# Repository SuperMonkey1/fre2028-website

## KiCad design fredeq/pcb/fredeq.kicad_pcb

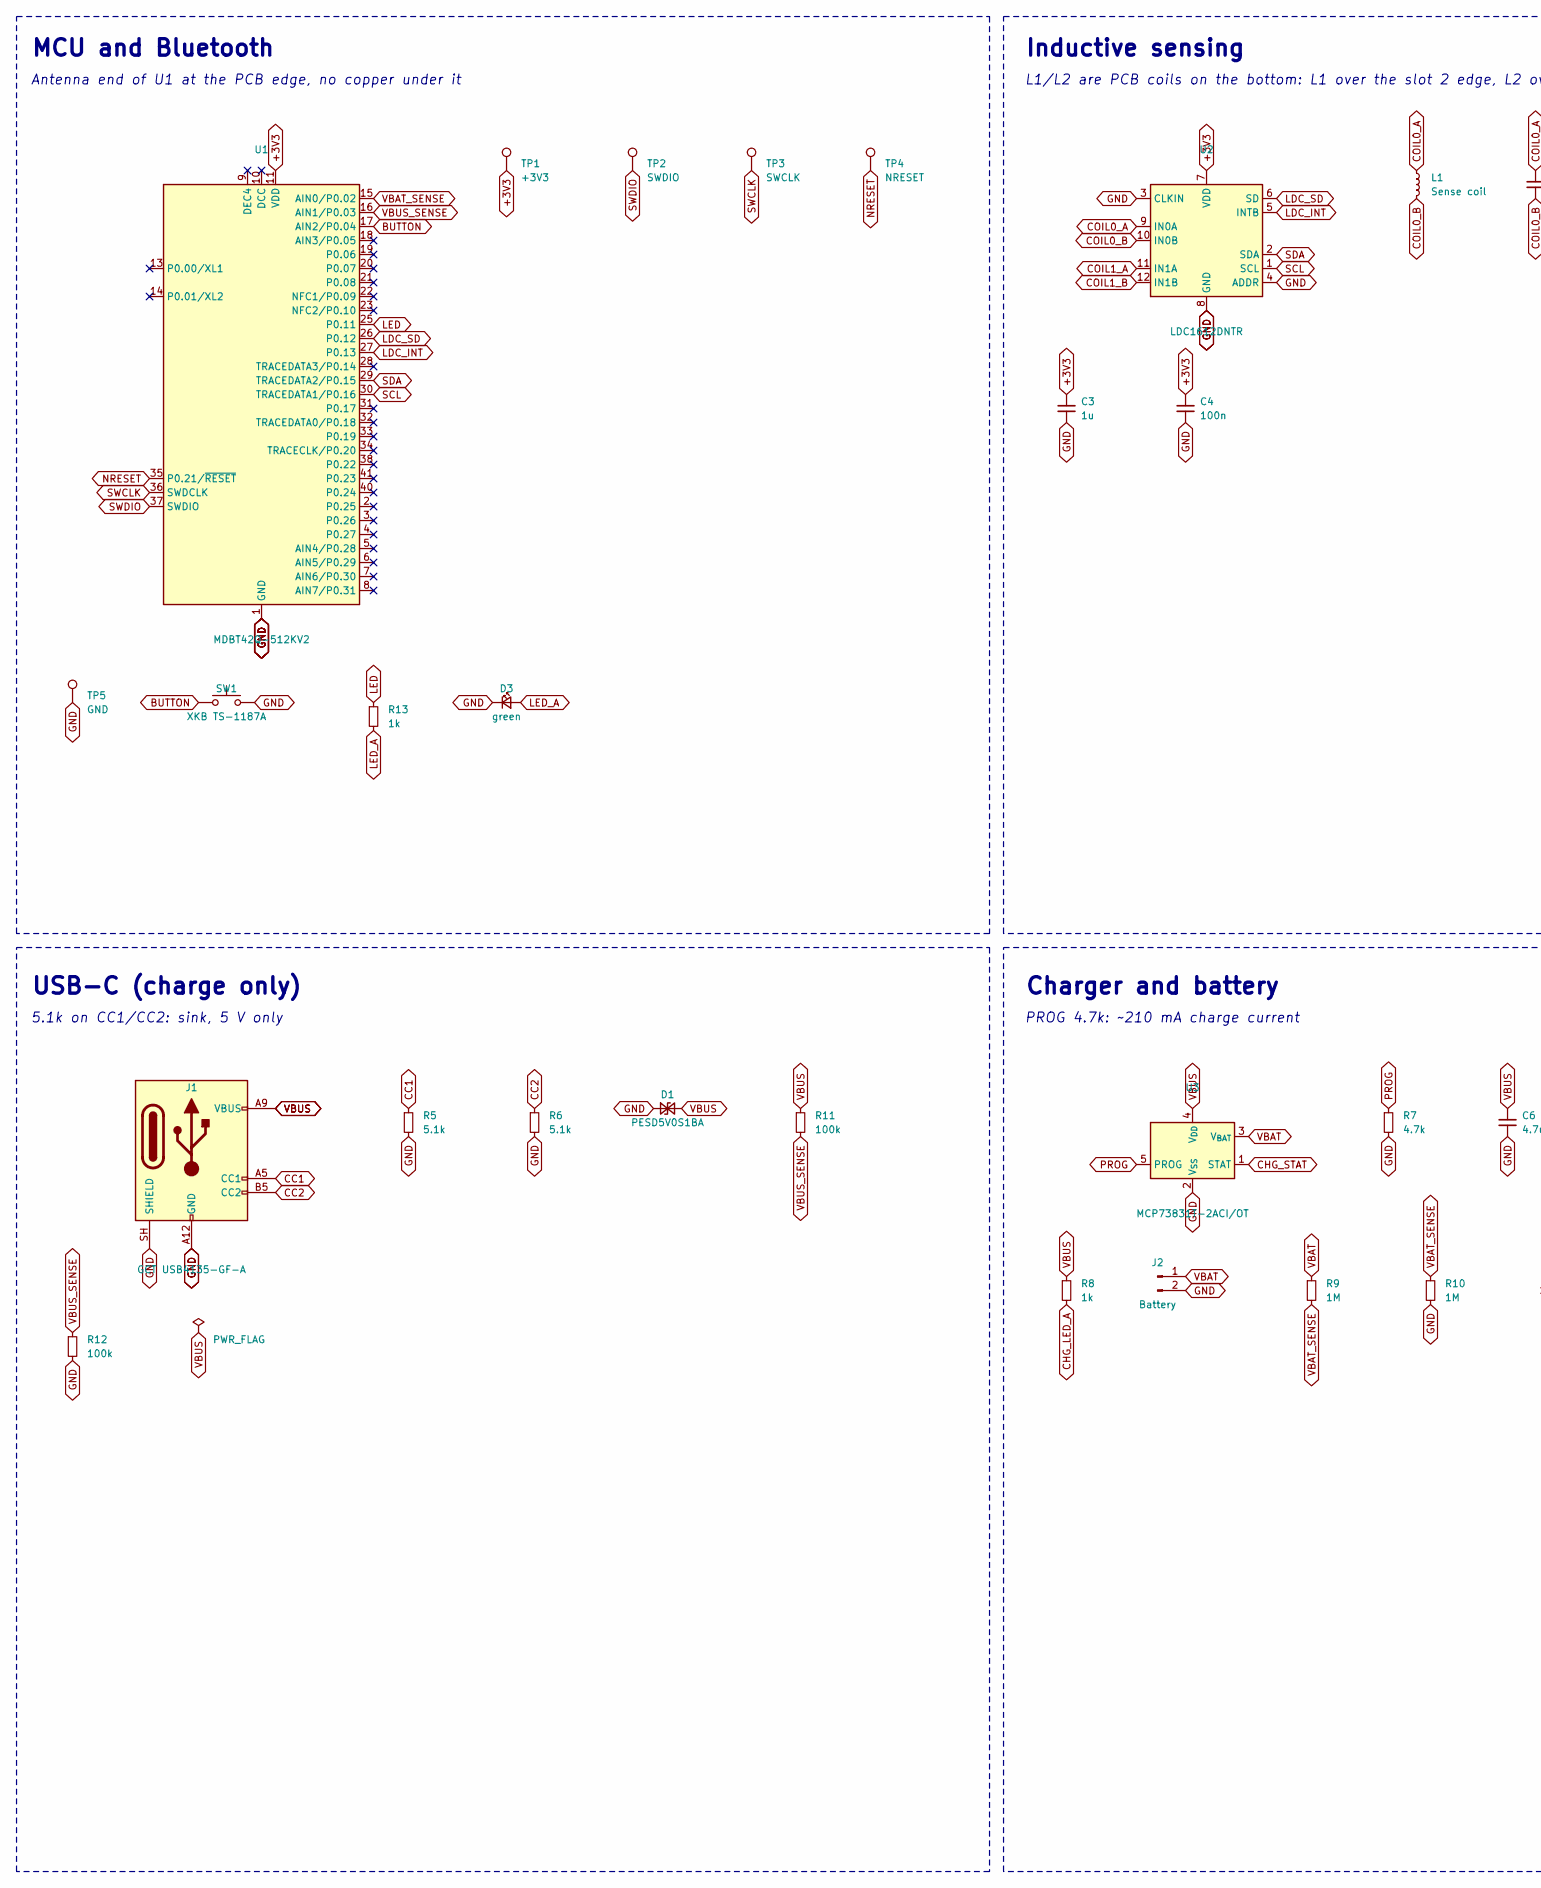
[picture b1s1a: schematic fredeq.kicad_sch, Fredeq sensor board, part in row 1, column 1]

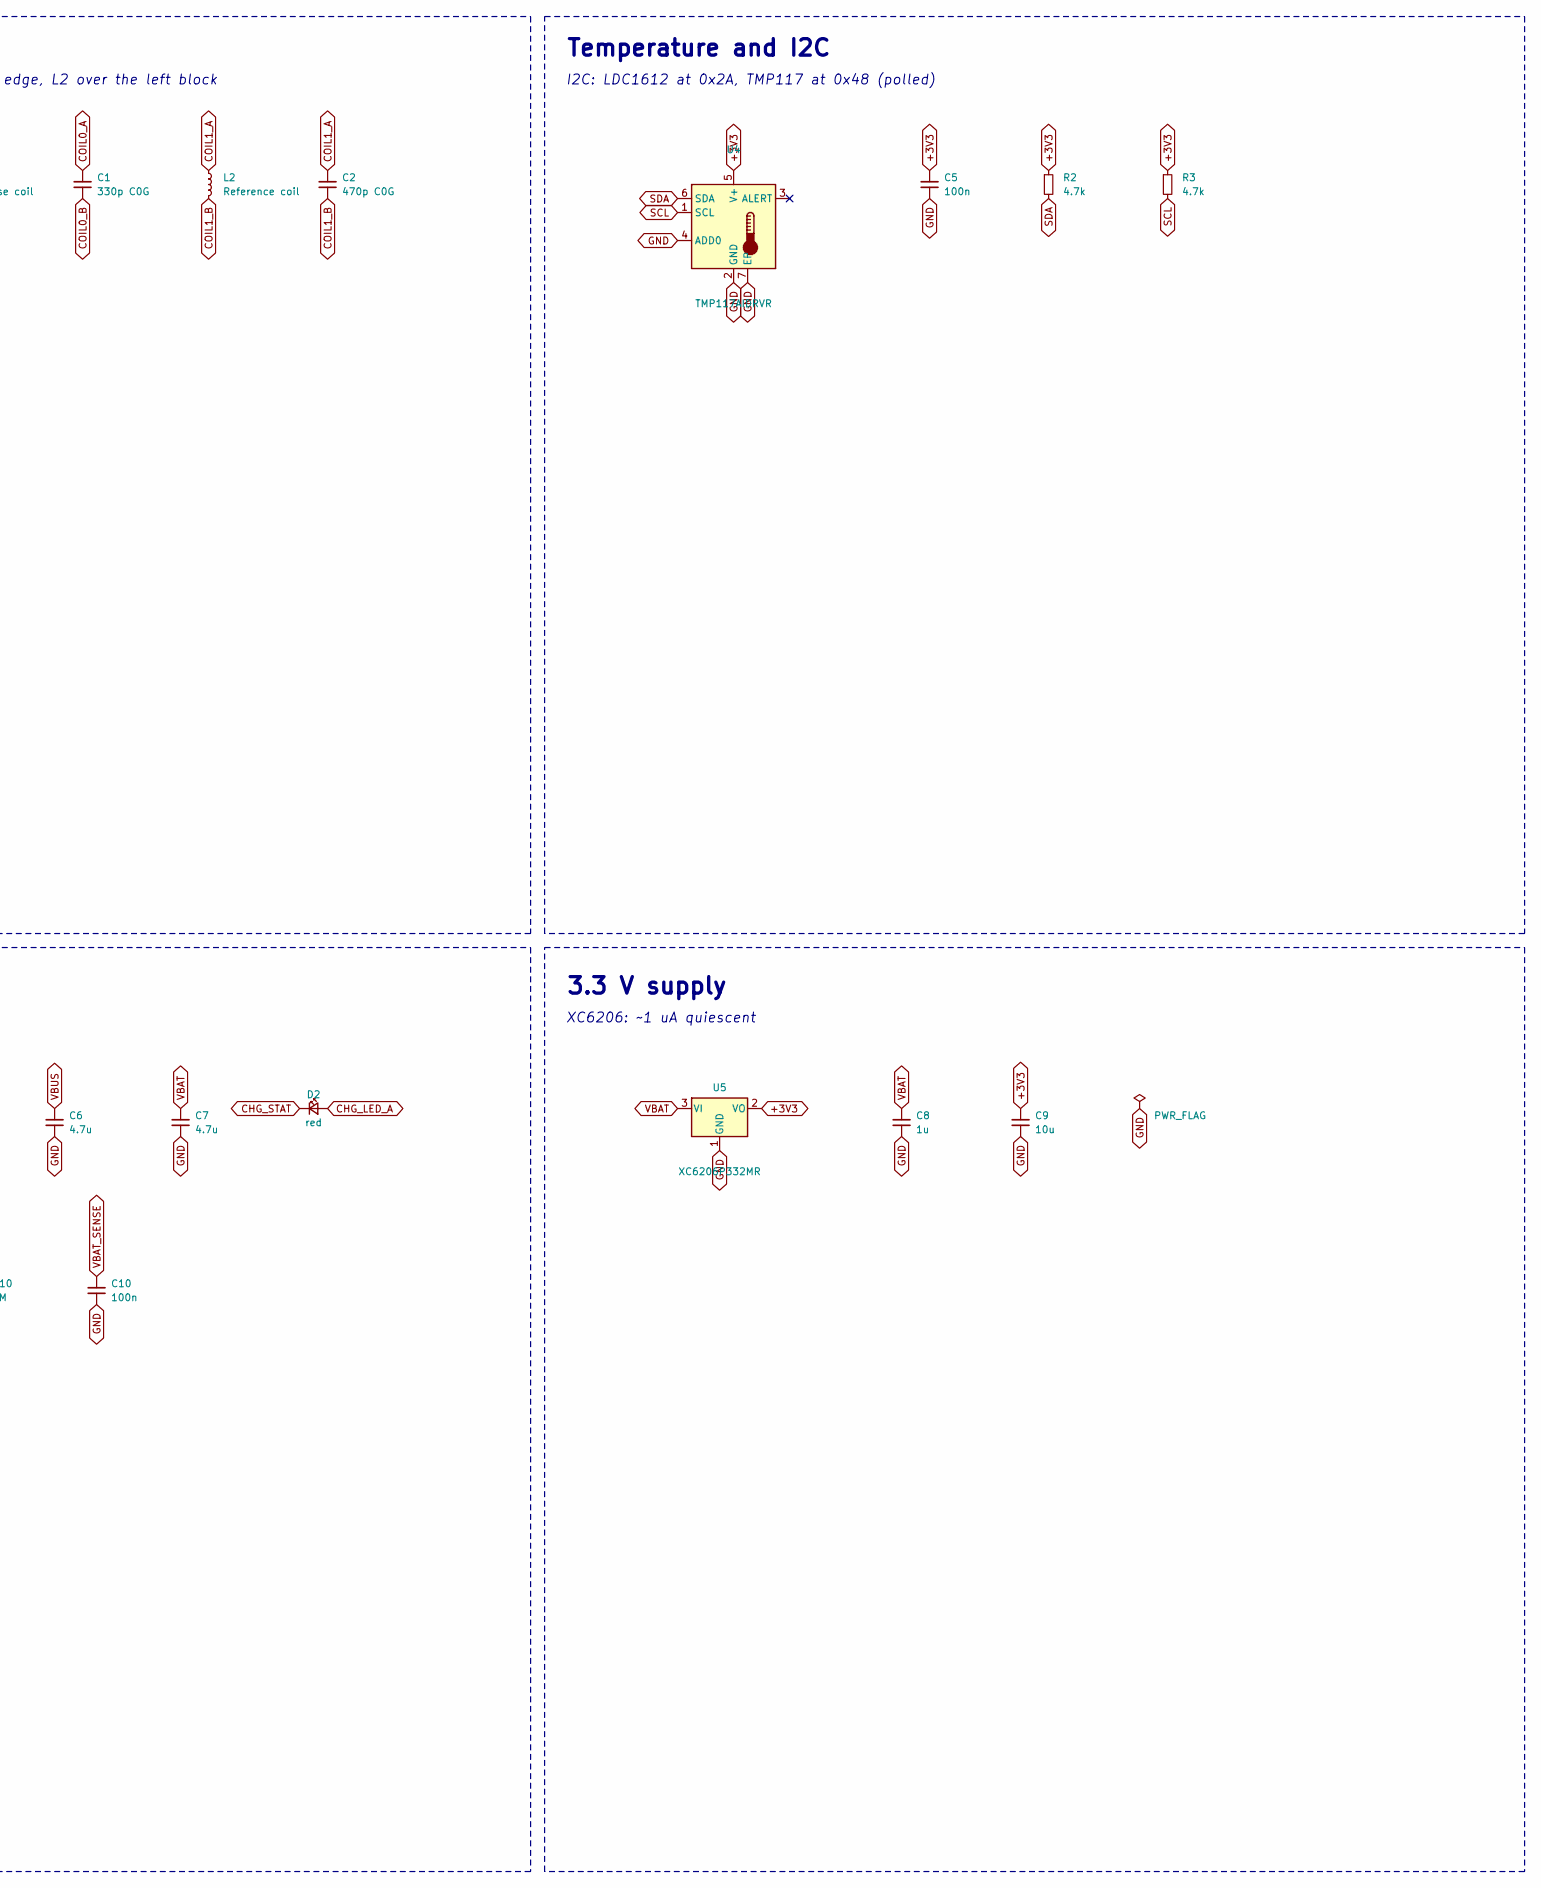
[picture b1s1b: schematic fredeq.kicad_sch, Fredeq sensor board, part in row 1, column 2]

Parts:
C1: 330p C0G; C_0402_1005Metric
C2: 470p C0G; C_0402_1005Metric
C3, C8: 1u; C_0402_1005Metric
C4, C5, C10: 100n; C_0402_1005Metric
C6, C7: 4.7u; C_0603_1608Metric
C9: 10u; C_0603_1608Metric
D1: PESD5V0S1BA; D_SOD-323
D2: red; LED_0603_1608Metric
D3: green; LED_0603_1608Metric
J1: GCT USB4135-GF-A; USB_C_Receptacle_GCT_USB4135-GF-A_6P_TopMnt_Horizontal
J2: Battery; JST_SH_SM02B-SRSS-TB_1x02-1MP_P1.00mm_Horizontal
L1: Sense coil; Coil_Sense_6x9mm
L2: Reference coil; Coil_Ref_4.4x10mm
R2, R3, R7: 4.7k; R_0402_1005Metric
R5, R6: 5.1k; R_0402_1005Metric
R8, R13: 1k; R_0402_1005Metric
R9, R10: 1M; R_0402_1005Metric
R11, R12: 100k; R_0402_1005Metric
SW1: XKB TS-1187A; SW_Push_1P1T_XKB_TS-1187A
TP1: +3V3; TestPoint_Pad_D1.0mm
TP2: SWDIO; TestPoint_Pad_D1.0mm
TP3: SWCLK; TestPoint_Pad_D1.0mm
TP4: NRESET; TestPoint_Pad_D1.0mm
TP5: GND; TestPoint_Pad_D1.0mm
U1: MDBT42Q-512KV2; Raytac_MDBT42Q
U2: LDC1612DNTR; WSON-12-1EP_4x4mm_P0.5mm_EP2.6x3mm
U3: MCP73831T-2ACI/OT; SOT-23-5
U4: TMP117AIDRVR; WSON-6-1EP_2x2mm_P0.65mm_EP1x1.6mm
U5: XC6206P332MR; SOT-23-3

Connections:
+3V3: C3.1, C4.1, C5.1, C9.1, R2.1, R3.1, TP1.1, U1.11 (VDD), U2.7 (VDD), U4.5 (V+), U5.2 (VO)
BUTTON: SW1.1, U1.17 (AIN2/P0.04)
CC1: J1.A5 (CC1), R5.1
CC2: J1.B5 (CC2), R6.1
CHG_LED_A: D2.2 (A), R8.2
CHG_STAT: D2.1 (K), U3.1 (STAT)
COIL0_A: C1.1, L1.1, U2.9 (IN0A)
COIL0_B: C1.2, L1.2, U2.10 (IN0B)
COIL1_A: C2.1, L2.1, U2.11 (IN1A)
COIL1_B: C2.2, L2.2, U2.12 (IN1B)
GND: C3.2, C4.2, C5.2, C6.2, C7.2, C8.2, C9.2, C10.2, D1.1 (A1), D3.1 (K), J1.A12 (GND), J1.B12 (GND), J1.SH (SHIELD), J2.2, R5.2, R6.2, R7.2, R10.2, R12.2, SW1.2, TP5.1, U1.1 (GND), U1.12 (GND), U1.24 (GND), U1.39 (GND), U2.3 (CLKIN), U2.4 (ADDR), U2.8 (GND), U2.13 (GND), U3.2 (V_{SS}), U4.2 (GND), U4.4 (ADD0), U4.7 (EP), U5.1 (GND)
LDC_INT: U1.27 (P0.13), U2.5 (INTB)
LDC_SD: U1.26 (P0.12), U2.6 (SD)
LED: R13.1, U1.25 (P0.11)
LED_A: D3.2 (A), R13.2
NRESET: TP4.1, U1.35 (P0.21/~RESET)
PROG: R7.1, U3.5 (PROG)
SCL: R3.2, U1.30 (TRACEDATA1/P0.16), U2.1 (SCL), U4.1 (SCL)
SDA: R2.2, U1.29 (TRACEDATA2/P0.15), U2.2 (SDA), U4.6 (SDA)
SWCLK: TP3.1, U1.36 (SWDCLK)
SWDIO: TP2.1, U1.37 (SWDIO)
VBAT: C7.1, C8.1, J2.1, R9.1, U3.3 (V_{BAT}), U5.3 (VI)
VBAT_SENSE: C10.1, R9.2, R10.1, U1.15 (AIN0/P0.02)
VBUS: C6.1, D1.2 (A2), J1.A9 (VBUS), J1.B9 (VBUS), R8.1, R11.1, U3.4 (V_{DD})
VBUS_SENSE: R11.2, R12.1, U1.16 (AIN1/P0.03)

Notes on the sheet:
MCU and Bluetooth
Antenna end of U1 at the PCB edge, no copper under it
Inductive sensing
L1/L2 are PCB coils on the bottom: L1 over the slot 2 edge, L2 over the left block
Temperature and I2C
I2C: LDC1612 at 0x2A, TMP117 at 0x48 (polled)
USB-C (charge only)
5.1k on CC1/CC2: sink, 5 V only
Charger and battery
PROG 4.7k: ~210 mA charge current
3.3 V supply
XC6206: ~1 uA quiescent

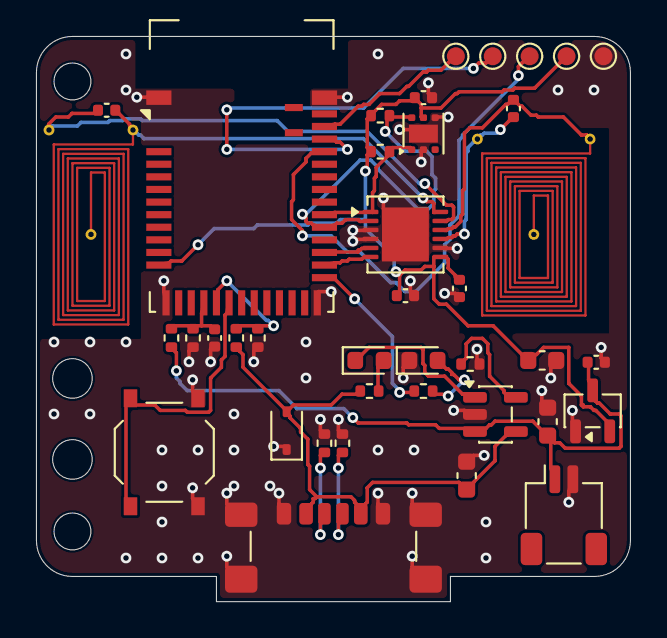
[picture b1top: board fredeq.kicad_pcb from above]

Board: 2 copper layers, 33.0 x 31.4 mm, 43 parts (0 on the bottom side), 25 nets.

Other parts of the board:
H1, H4: Hole_Pin_2.05mm
H2, H3: Hole_M2_Screw

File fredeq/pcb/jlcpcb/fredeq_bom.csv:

Comment,Designator,Footprint,LCSC Part #
330p C0G,C1,C_0402_1005Metric,C5591231
470p C0G,C2,C_0402_1005Metric,C75274
1u,"C3,C8",C_0402_1005Metric,C52923
100n,"C4,C5,C10",C_0402_1005Metric,C1525
4.7u,"C6,C7",C_0603_1608Metric,C19666
10u,C9,C_0603_1608Metric,C19702
PESD5V0S1BA,D1,D_SOD-323,C19224
red,D2,LED_0603_1608Metric,C2286
green,D3,LED_0603_1608Metric,C72043
Battery,J2,JST_SH_SM02B-SRSS-TB_1x02-1MP_P1.00mm_Horizontal,C160402
100k,"R11,R12",R_0402_1005Metric,C25741
4.7k,"R2,R3,R7",R_0402_1005Metric,C25900
5.1k,"R5,R6",R_0402_1005Metric,C25905
1k,"R8,R13",R_0402_1005Metric,C11702
1M,"R9,R10",R_0402_1005Metric,C26083
XKB TS-1187A,SW1,SW_Push_1P1T_XKB_TS-1187A,C318884
LDC1612DNTR,U2,WSON-12-1EP_4x4mm_P0.5mm_EP2.6x3mm,C1847959
MCP73831T-2ACI/OT,U3,SOT-23-5,C424093
TMP117AIDRVR,U4,WSON-6-1EP_2x2mm_P0.65mm_EP1x1.6mm,C699536
XC6206P332MR,U5,SOT-23-3,C5446

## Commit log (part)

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2025-10-23 Initial commit: Fré Leys climbing portfolio website
2025-10-23 added newsletter modal
2025-10-23 email feature V1
2025-10-23 newsletter finished
2025-10-23 big css update
2025-10-23 home page improvements
2025-10-27 main page improvements
2025-10-27 SEO optimization
2025-10-27 partners page
2025-10-27 admin panel
2025-10-27 deleted
2025-10-27 cms load
2025-10-27 todo
2025-10-28 content 1
2025-10-28 media
2025-10-28 some bug fixes
2025-10-29 picture improvements
2025-11-01 partners explenation
2025-11-01 improvements
2025-11-02 documentation
2025-11-02 Your commit message
2025-11-02 blog finished
2025-11-02 repove
2025-11-02 fun image for sponsors
2025-11-02 improved images
2025-11-15 content and story changes
2025-11-16 brochure half way
2025-11-16 brochure finished
2025-11-19 social media posts launch
2025-11-23 ARTIKEL
2026-01-05 com en partners
2026-03-10 tedx
2026-03-12 mails
2026-03-31 hoppa
